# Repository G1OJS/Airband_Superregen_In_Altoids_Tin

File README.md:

# G1OJS VHF Airband Superregen Receiver

Last summer (2023) I got the construction bug and wanted to build an airband receiver free from microprocessors. Something with an "analogue feel". 
So I set about Googling and found quite a few designs for superregen receivers and a particular superhet kit that comes up very often based around
the NE602 oscillator/mixer and several op-amps, plus an "IF can" transformer. I wanted to make something that was as close to an all-transistor all-solid-state design as I could (in other words, things I had to hand!). 

At the time (despite being a Ham since 1984 and an electronics engineering graduate) I hadn't realised that a SuperRegenerative receiver is very different from a Regenerative Receiver. Key things I leaned straightaway - a superregen receiver:

- doesn't have a "regen" control that allows the circuit to behave as a high Q AM receiver which can tip into self oscillation and become a DSB receiver. A superregen is an AM receiver (which can also be used on FM via slope detection), and its operating point is set internally.
- has a kind of "capture effect" which causes the receiver to focus on the strongest signal in the passband
- can be almost as sensitive as any other receiver
- has a log law response to RF signal level, meaning good dynamic range without need of an AGC

One of the best explanations of how these receivers actually *work* is a paper called "Designing Super-Regenerative Receivers" by Dr Eddie Insam. There is a copy [here](https://www.qsl.net/l/lu7did/docs/QRPp/Receptor%20Regenerativo.pdf). Don't be put off by the maths because the text explains things well.

The circuit used above started off as my build of a circuit found at lots of places online, all variants of this one described in [Radio Builder](https://radiobuilder.blogspot.com/2012/10/airbandregen1t.html). Some of the variants have quite strange and unnecessary variations! There is nothing critical - nor magical - about the twisted and folded antenna found in some versions that don't have the RF isolator/amplifier. 

I added an RF gain stage and two-transistor audio amplifier, and spent *a lot* of time investigating the effect of changing the component values in the quench frequency components and audio tap. The circuit I ended up with is below, and it works really well:

Construction note: keep leads short as possible in the RF parts (first two transistors). If you find the 10pF capacitor connected to the varicap diode in the photo above, you'll see that the path to ground via that capacitor and the varicap diode is a lot shorter than it appears from the circuit diagram. 

This little receiver has quite a few advantages:
- Current draw only about 9 mA
- Capture effect combined with wide passband makes for easy yet selective tuning
- Fun to build with only 4 transistors & a handful of R, L, C.
- Almost as sensitive as any other receiver
- No IF frequency therefore no image filtering required & no problems with pager system images etc

It does of course have disadvantages. One is that it can be overwhelmed by strong signals if connected to a large antenna. Another is that stray capacitance and lead inductance play affect the performance such that different layouts will behave slightly differently. But for a hand portable with a quarter wave whip, it's a lot of fun. It's even possible to add a squelch circuit, but this requires a whole IC and Rs and Cs & is a bit fiddly to operate, though it does work (page coming on this soon, maybe).

Note: as with all superregen receivers, the superregen stage oscillates with a lot of amplitude at the receive frequency and across a lot of adjacent spectrum. If used close to airports, it must be in a screened box and any antenna must be isolated by using an input amplifier/isolator as shown.

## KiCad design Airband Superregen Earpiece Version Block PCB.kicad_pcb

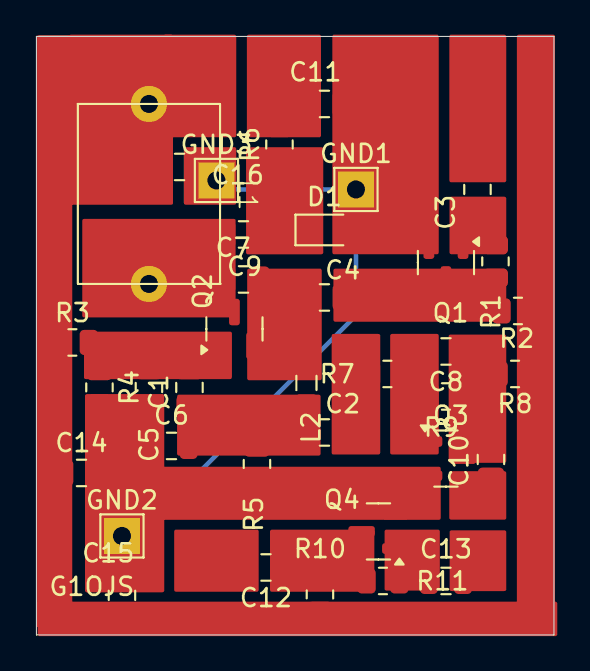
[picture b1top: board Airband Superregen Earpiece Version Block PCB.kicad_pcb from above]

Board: 2 copper layers, 28.8 x 33.2 mm, 37 parts (0 on the bottom side), 15 nets.

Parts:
C1: 6n8; C_0805_2012Metric
C2, C12, C15: 3u3; C_0805_2012Metric
C3: 33p; C_0805_2012Metric
C4: 5pF; C_0805_2012Metric
C5, C10, C11, C13, C14, C16: 100n; C_0805_2012Metric
C6: 22n; C_0805_2012Metric
C7: 2p2; C_0805_2012Metric
C8: 2n2; C_0805_2012Metric
C9: 15p; C_0805_2012Metric
D1: BB910; D_SOD-323
GND1, GND2, GND3: GND; TestPoint_THTPad_2.0x2.0mm_Drill1.0mm
L1: 5t 6mm dia; Inductor_Axial_L10.0mm_D7.9mm_P10.0mm_Horizontal
L2: 12uH; L_0805_2012Metric
Q1: 2SC3356; SOT-23
Q2, Q3, Q4: MMBT3904; SOT-23
R1: 68k; R_0805_2012Metric
R2: 1k; R_0805_2012Metric
R3, R4: 22k; R_0805_2012Metric
R5: 10k; R_0805_2012Metric
R6, R9, R11: 470k; R_0805_2012Metric
R7, R8, R10: 2k2; R_0805_2012Metric

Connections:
Chassis: C5.2, C6.2, C11.2, C14.2, C15.2, C16.2, D1.2 (A), GND1.1, GND2.1, GND3.1, Q1.2 (E), Q3.2 (E), Q4.2 (E), R4.2, R5.2
unnamed: C1.2, C2.1, C6.1, L2.2, R5.1
unnamed: C2.2, R7.1
unnamed: C11.1, R6.2
unnamed: C14.1, C15.1, C16.1, L1.1, R2.1, R3.1, R8.1, R10.1
unnamed: C9.2, D1.1 (K), R6.1
unnamed: C3.2, Q1.1 (B), R1.2
unnamed: C4.1, Q1.3 (C), R1.1, R2.2
unnamed: C1.1, C5.1, Q2.1 (B), R3.2, R4.1
unnamed: C7.2, C9.1, L1.2, Q2.3 (C)
unnamed: C4.2, C7.1, L2.1, Q2.2 (E)
unnamed: C8.2, Q3.1 (B), R7.2, R9.2
unnamed: C8.1, C10.2, Q3.3 (C), R8.2, R9.1
unnamed: C13.1, Q4.1 (B), R11.2
unnamed: C12.1, Q4.3 (C), R10.2, R11.1

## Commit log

2025-07-13 Add local files
